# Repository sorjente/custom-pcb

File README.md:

# Custom STM32L4 PCB

## What?

This is an attempt to build a minimal, custom PCB featuring an STM32L4 MCU, using (ideally only) open source tools.
It will hopefully serve as a stepping stone to build more complex embedded systems.

## Why?

Because learning is fun.

## Who?

[@ayoubsabri](https://ayoubsabri.github.io/) & [@kokkonisd](https://kokkonisd.github.io/).

---

## Setting up this project

To set up this project, you can start by cloning it:

```
$ git clone https://github.com/kokkonisd/custom-pcb
```

You then need to pull `libopencm3`. You can do this by running `make` in `hello_opencm3/`, or do it manually:

```
$ git submodule init
$ git submodule update
$ cd hello_opencm3/libopencm3/ && make
```

You only need to do this once.

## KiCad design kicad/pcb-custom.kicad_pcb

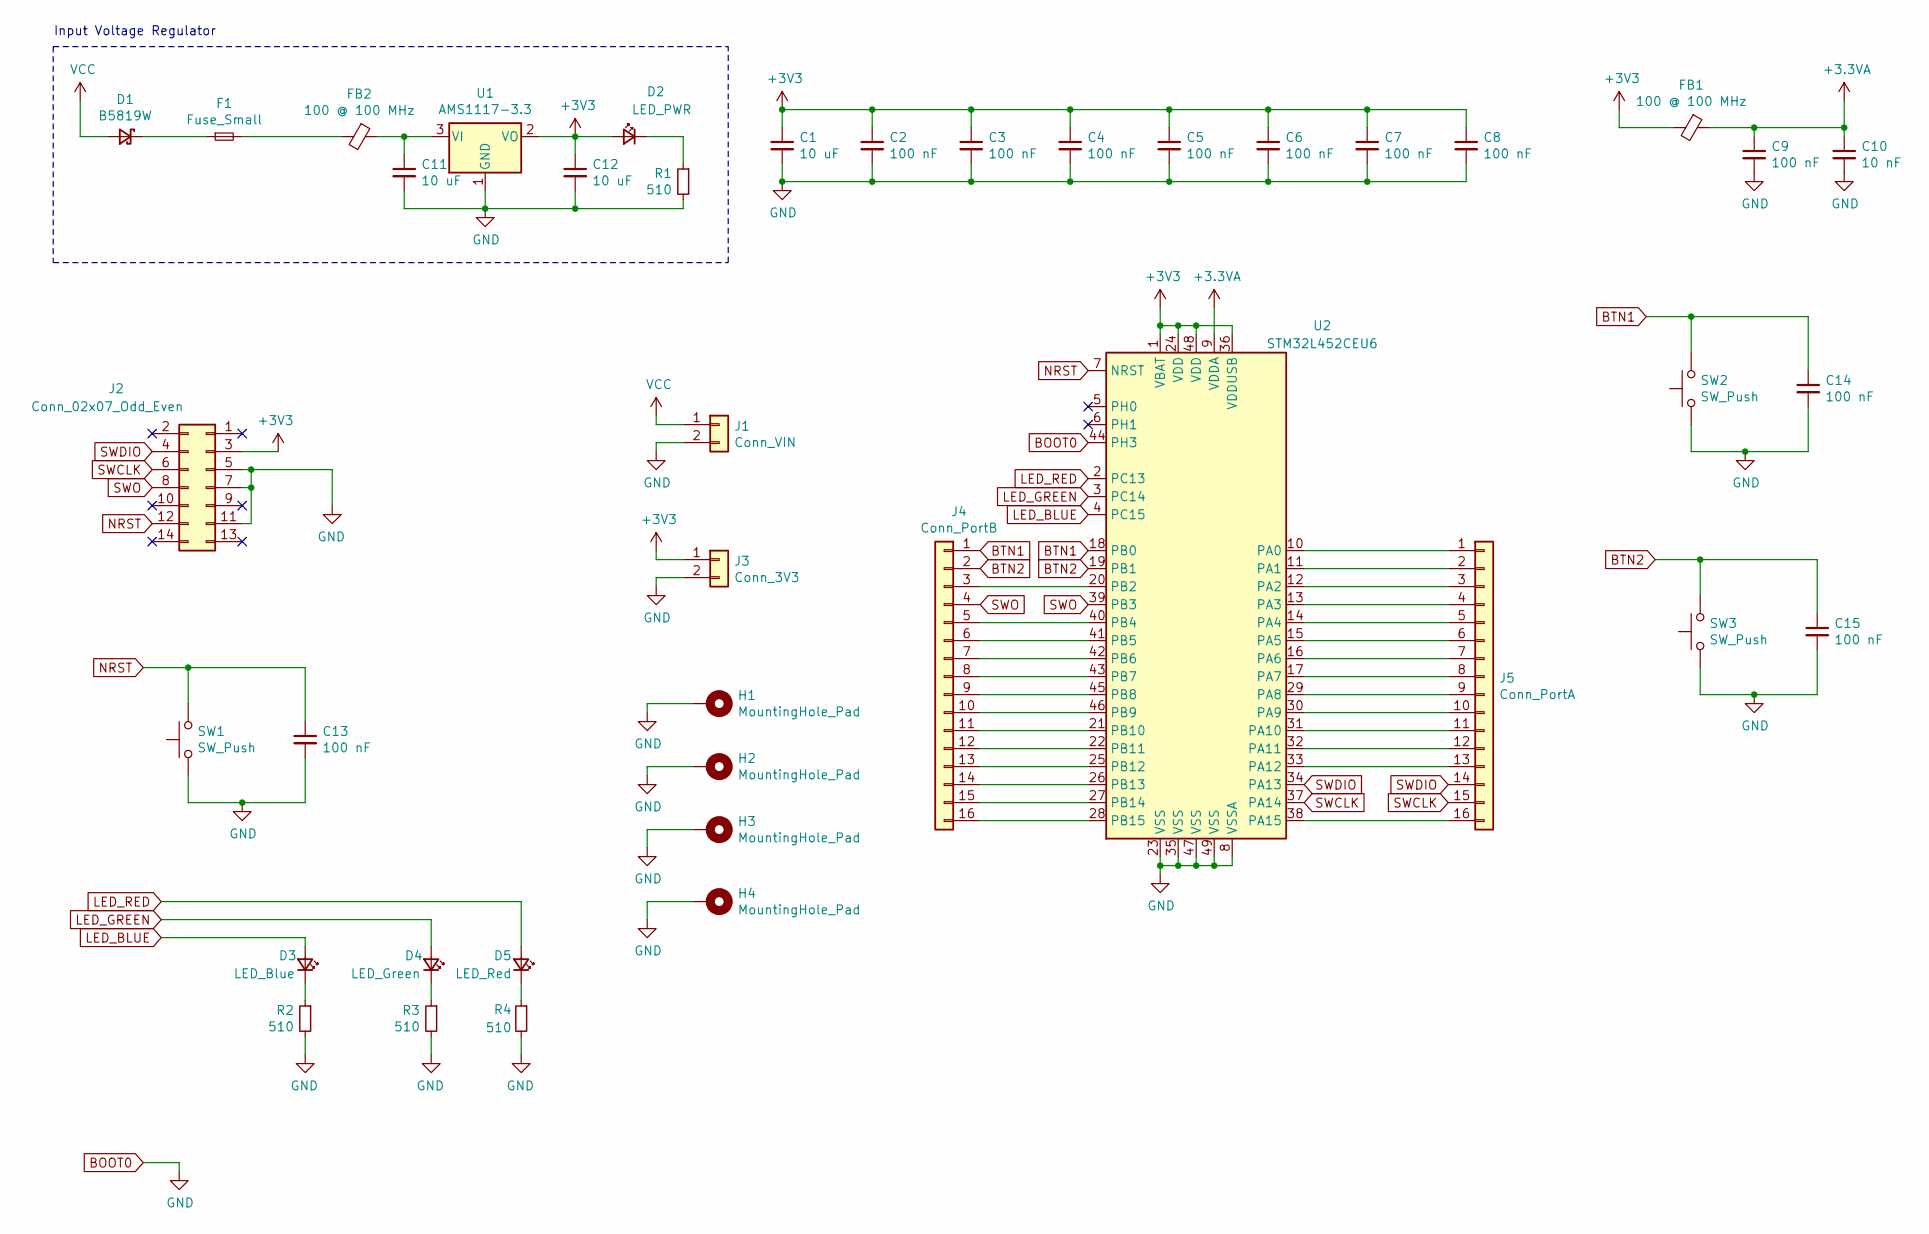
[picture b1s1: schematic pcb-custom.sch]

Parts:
C1, C11, C12: 10 uF; C_0805_2012Metric
C2, C3, C4, C5, C6, C7, C8, C9, C13, C14, C15: 100 nF; C_0402_1005Metric
C10: 10 nF; C_0402_1005Metric
D1: B5819W; D_SOD-123
D2: LED_PWR; LED_0603_1608Metric
D3: LED_Blue; LED_0603_1608Metric
D4: LED_Green; LED_0603_1608Metric
D5: LED_Red; LED_0603_1608Metric
F1: Fuse_Small; Fuse_0603_1608Metric
FB1, FB2: 100 @ 100 MHz; L_0805_2012Metric
H1, H2, H3, H4: MountingHole_Pad; MountingHole_4.3mm_M4_Pad_Via
J1: Conn_VIN; PinHeader_1x02_P2.54mm_Vertical
J2: Conn_02x07_Odd_Even; PinHeader_2x07_P1.27mm_Vertical
J3: Conn_3V3; PinHeader_1x02_P2.54mm_Vertical
J4: Conn_PortB; PinHeader_1x16_P2.54mm_Vertical
J5: Conn_PortA; PinHeader_1x16_P2.54mm_Vertical
R1, R2, R3, R4: 510; R_0603_1608Metric
SW1, SW2, SW3: SW_Push; SW_SPST_EVQP0
U1: AMS1117-3.3; SOT-223-3_TabPin2
U2: STM32L452CEU6; QFN-48-1EP_7x7mm_P0.5mm_EP5.6x5.6mm

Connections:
+3.3VA: C9.1, C10.1, FB1.1, U2.9 (VDDA)
+3V3: C1.1, C2.1, C3.1, C4.1, C5.1, C6.1, C7.1, C8.1, C12.1, D2.2 (A), FB1.2, J2.3, J3.1, U1.2 (VO), U2.1 (VBAT), U2.24 (VDD), U2.36 (VDDUSB), U2.48 (VDD)
BOOT0: C1.2, C2.2, C3.2, C4.2, C5.2, C6.2, C7.2, C8.2, C9.2, C10.2, C11.2, C12.2, C13.2, C14.2, C15.2, H1.1, H2.1, H3.1, H4.1, J1.2, J2.5, J2.7, J2.11, J3.2, R1.2, R2.2, R3.2, R4.2, SW1.1, SW2.1, SW3.1, U1.1 (GND), U2.8 (VSSA), U2.23 (VSS), U2.35 (VSS), U2.44 (PH3), U2.47 (VSS), U2.49 (VSS)
BTN1: C14.1, J4.1, SW2.2, U2.18 (PB0)
BTN2: C15.1, J4.2, SW3.2, U2.19 (PB1)
LED_BLUE: D3.2 (A), U2.4 (PC15)
LED_GREEN: D4.2 (A), U2.3 (PC14)
LED_RED: D5.2 (A), U2.2 (PC13)
NRST: C13.1, J2.12, SW1.2, U2.7 (NRST)
unnamed: C11.1, FB2.1, U1.3 (VI)
unnamed: D1.1 (K), F1.1
unnamed: D2.1 (K), R1.1
unnamed: D3.1 (K), R2.1
unnamed: D4.1 (K), R3.1
unnamed: D5.1 (K), R4.1
unnamed: F1.2, FB2.2
unnamed: J4.3, U2.20 (PB2)
unnamed: J4.5, U2.40 (PB4)
unnamed: J4.6, U2.41 (PB5)
unnamed: J4.7, U2.42 (PB6)
unnamed: J4.8, U2.43 (PB7)
unnamed: J4.9, U2.45 (PB8)
unnamed: J4.10, U2.46 (PB9)
unnamed: J4.11, U2.21 (PB10)
unnamed: J4.12, U2.22 (PB11)
unnamed: J4.13, U2.25 (PB12)
unnamed: J4.14, U2.26 (PB13)
unnamed: J4.15, U2.27 (PB14)
unnamed: J4.16, U2.28 (PB15)
unnamed: J5.1, U2.10 (PA0)
unnamed: J5.2, U2.11 (PA1)
unnamed: J5.3, U2.12 (PA2)
unnamed: J5.4, U2.13 (PA3)
unnamed: J5.5, U2.14 (PA4)
unnamed: J5.6, U2.15 (PA5)
unnamed: J5.7, U2.16 (PA6)
unnamed: J5.8, U2.17 (PA7)
unnamed: J5.9, U2.29 (PA8)
unnamed: J5.10, U2.30 (PA9)
unnamed: J5.11, U2.31 (PA10)
unnamed: J5.12, U2.32 (PA11)
unnamed: J5.13, U2.33 (PA12)
unnamed: J5.16, U2.38 (PA15)
SWCLK: J2.6, J5.15, U2.37 (PA14)
SWDIO: J2.4, J5.14, U2.34 (PA13)
SWO: J2.8, J4.4, U2.39 (PB3)
VCC: D1.2 (A), J1.1

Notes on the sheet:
Input Voltage Regulator

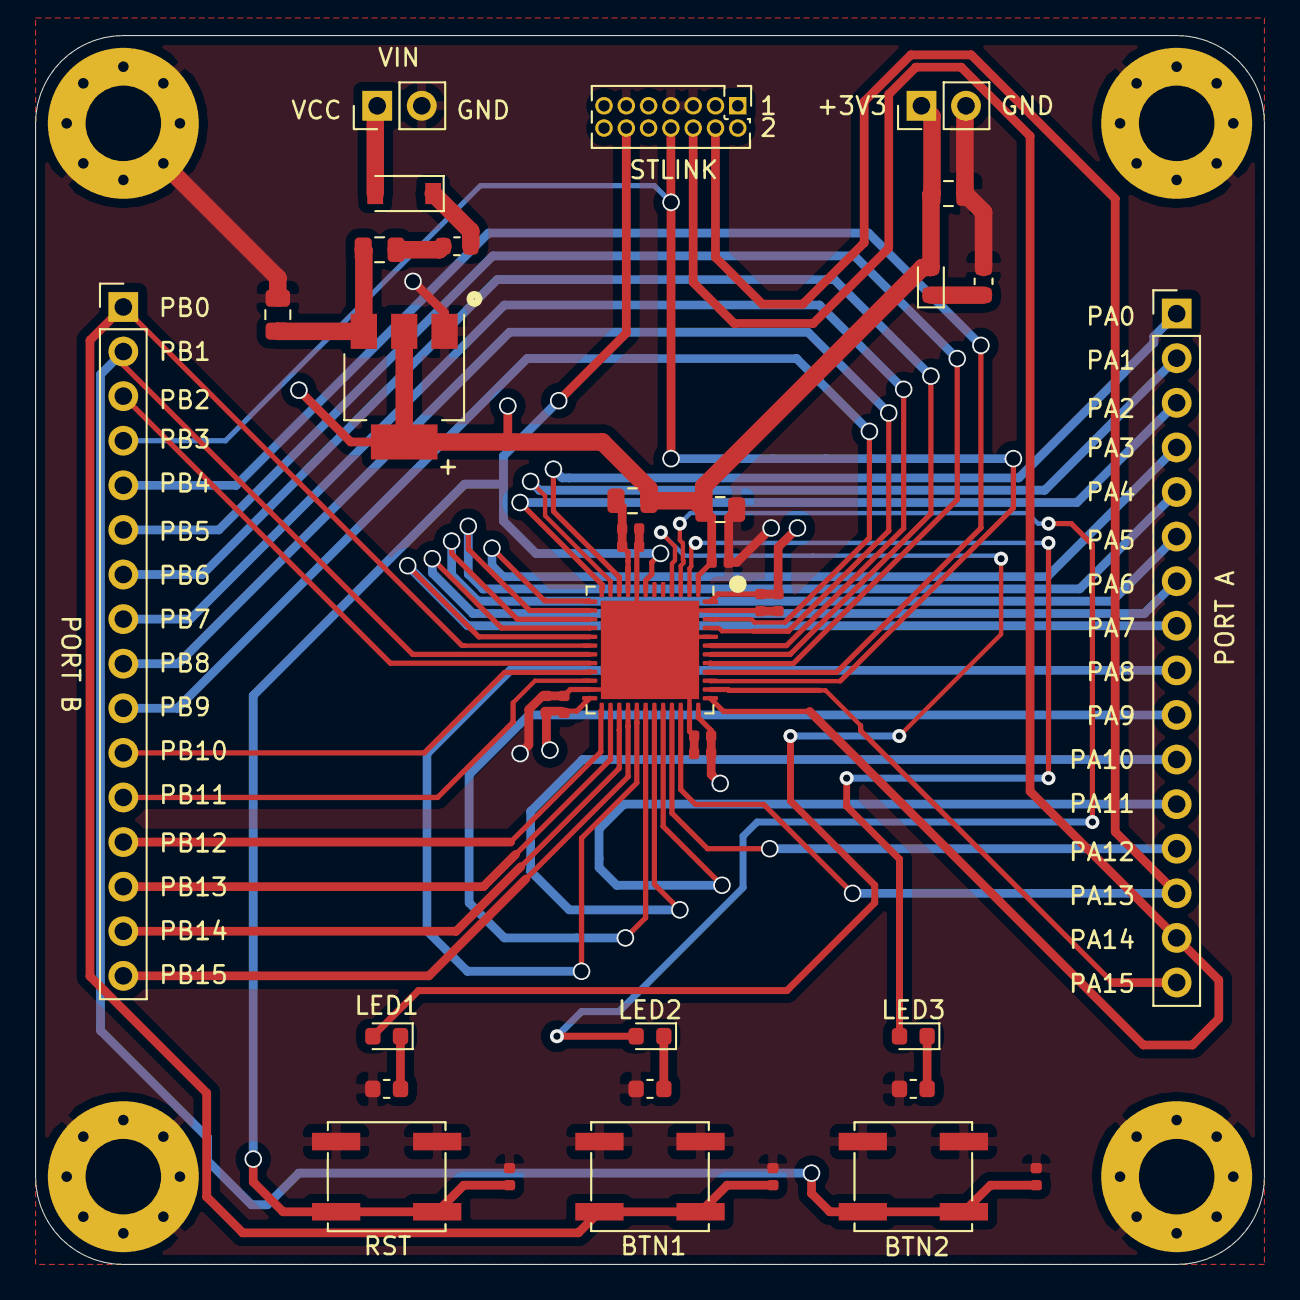
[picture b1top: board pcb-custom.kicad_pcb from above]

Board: 4 copper layers, 70.0 x 70.0 mm, 41 parts (0 on the bottom side), 47 nets.

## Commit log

2020-06-08 Import opencm3
2020-06-08 Add minimal blinky
2020-06-13 Why are all my objects discarded
2020-06-14 Write startup and linker scripts (broken)
2020-06-14 Add automatic pull & build of libopencm3, fix linker bug for isr_vector
2020-06-15 Add documentation
2020-06-15 Fix links in hello_opencm3's README
2020-06-15 Fix typo in link
2020-07-05 Add kicad project files
2020-07-05 Start routing
2020-07-19 Complete routing
